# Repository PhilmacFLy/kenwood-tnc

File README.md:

# kenwood-tnc
Simple TNC PCB to use a radio with a kenwood ptt connector with a pc to do packet radio

# Bill of Materials (BOM)

Qty | Value | Parts | URL (exemplary supplier)
:--:|:----- |:------|:------------------------
2   |1N 4148| D1,D2 |https://www.reichelt.de/schalt-diode-100-v-150-ma-do-35-1n-4148-p1730.html?&nbc=1
1   |2,20 kOhm| R1  |https://www.reichelt.de/widerstand-metallschicht-2-20-kohm-0207-0-6-w-1-metall-2-20k-p11584.html?&nbc=1
1   |47 uF  | C1    |https://www.reichelt.de/elko-radial-47-uf-50-v-105-c-low-esr-fr-a-47u-50-p200269.html?&nbc=1
1   |BC 547C| Q1    |https://www.reichelt.de/bipolartransistor-npn-45v-0-1a-0-5w-to-92-bc-547c-p5007.html?&nbc=1
1   |SUB-D9 | J1    |https://www.reichelt.de/d-sub-stecker-9-polig-gewinkelt-rm-2-77-d-sub-st-09eu-p6986.html?&nbc=1
4   |3.5 mm | J2,J3,J4,J5|https://www.reichelt.de/klinkenbuchse-stereo-3-pol-3-5-mm-cliff-fc68131-p228173.html?&nbc=1
2   |1kOhm  | RV1, RV2| https://www.reichelt.de/praezisionspotentiometer-trimmer-stehend-1-0-kohm-9-5-mm-76-40-1-0k-p3498.html?&nbc=1

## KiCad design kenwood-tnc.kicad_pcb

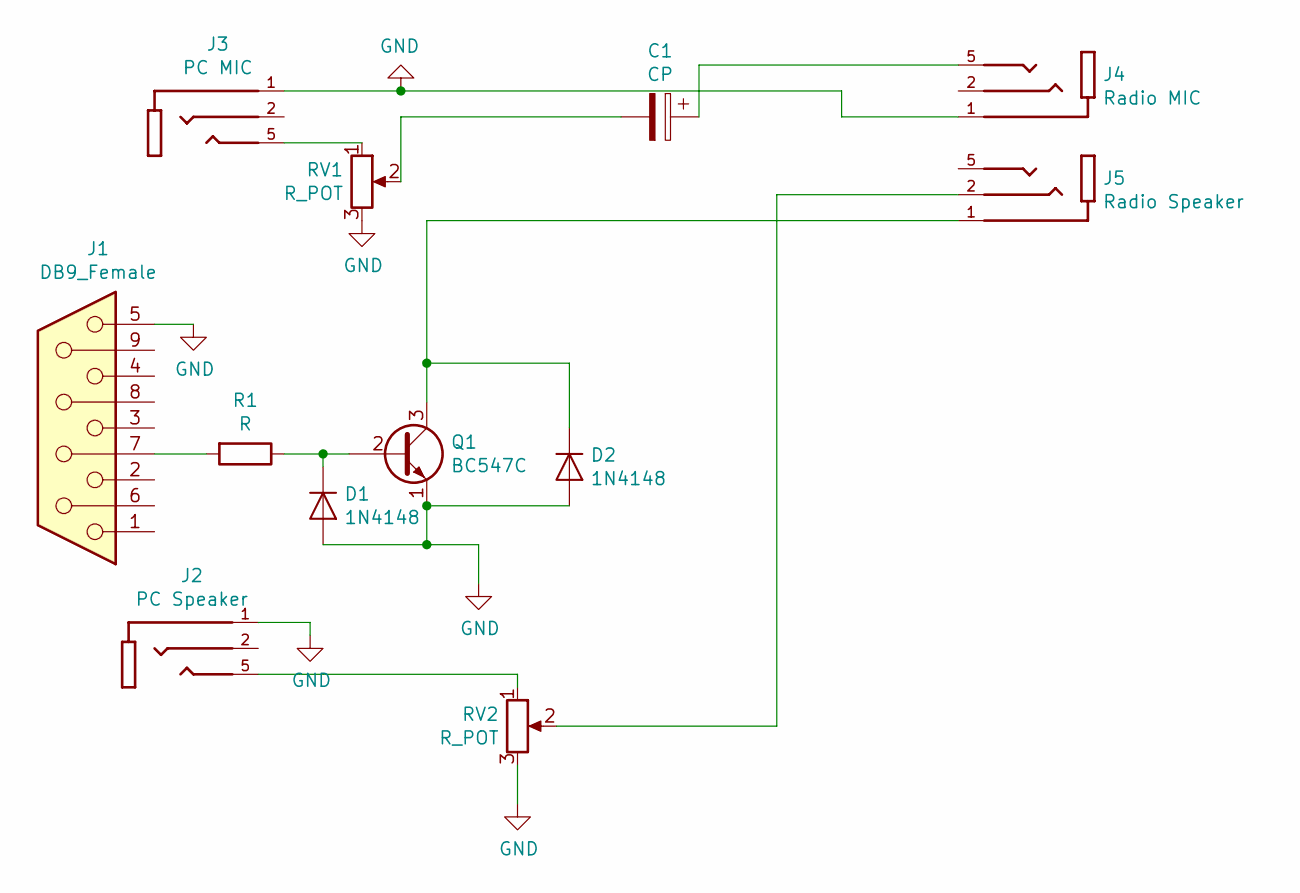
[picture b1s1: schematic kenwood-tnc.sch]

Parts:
C1: CP; CP_Radial_D6.3mm_P2.50mm
D1, D2: 1N4148; D_DO-35_SOD27_P7.62mm_Horizontal
J1: DB9_Female; DSUB-9_Female_Horizontal_P2.77x2.84mm_EdgePinOffset4.94mm_H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
J2: PC Speaker; CLIFF_FC68131
J3: PC MIC; CLIFF_FC68131
J4: Radio MIC; CLIFF_FC68131
J5: Radio Speaker; CLIFF_FC68131
Q1: BC547C; TO-92
R1: R; R_Axial_DIN0207_L6.3mm_D2.5mm_P7.62mm_Horizontal
RV1, RV2: R_POT; Potentiometer_Vishay_T73XW_Horizontal

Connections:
GND: D1.2 (A), D2.2 (A), J1.5, J2.1 (SLEEVE), J3.1 (SLEEVE), J4.1 (SLEEVE), Q1.1 (E), RV1.3, RV2.3
unnamed: C1.1, J4.5 (TIP)
unnamed: C1.2, RV1.2
unnamed: D1.1 (K), Q1.2 (B), R1.1
unnamed: D2.1 (K), J5.1 (SLEEVE), Q1.3 (C)
unnamed: J1.7, R1.2
unnamed: J2.5 (TIP), RV2.1
unnamed: J3.5 (TIP), RV1.1
unnamed: J5.2 (RING), RV2.2

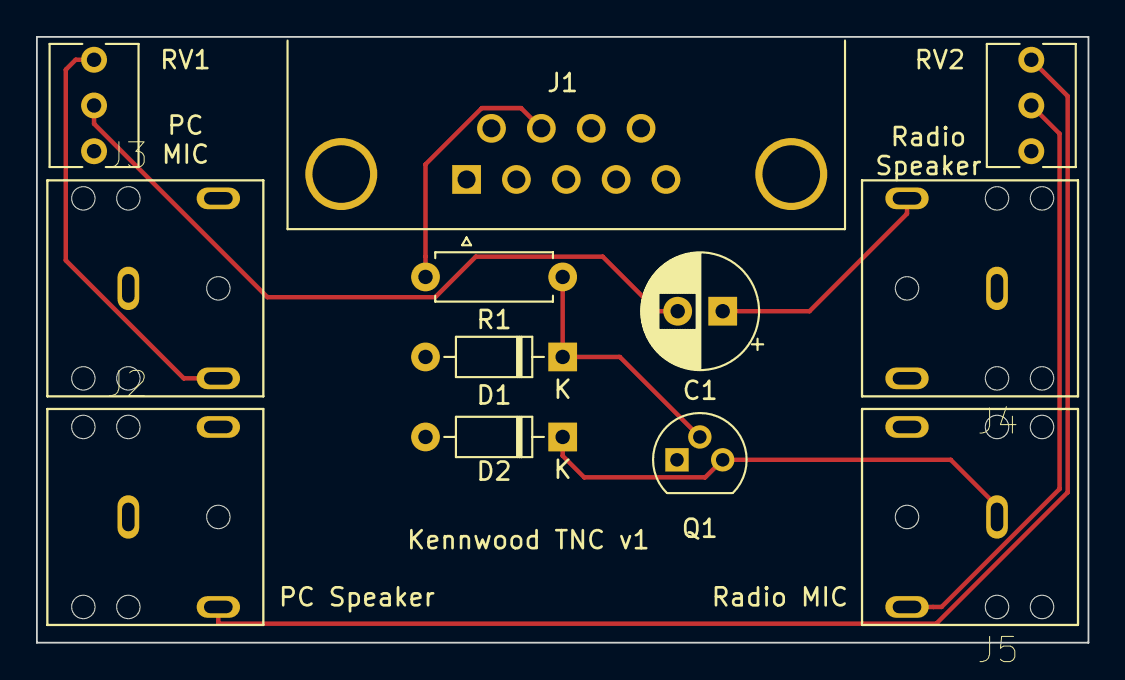
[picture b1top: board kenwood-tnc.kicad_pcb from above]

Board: 2 copper layers, 58.4 x 33.7 mm, 12 parts (0 on the bottom side), 9 nets.

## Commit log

2020-05-28 Added bom
2020-05-28 KiCAD update
